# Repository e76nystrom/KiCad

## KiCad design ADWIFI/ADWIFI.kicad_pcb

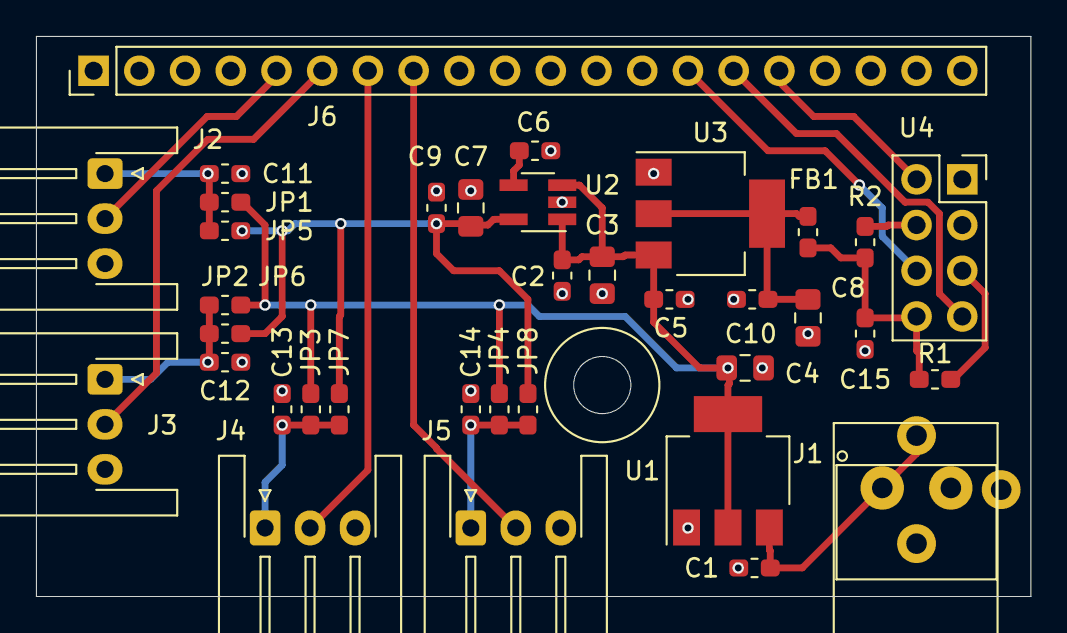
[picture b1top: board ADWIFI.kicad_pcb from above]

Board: 2 copper layers, 55.2 x 31.1 mm, 37 parts (0 on the bottom side), 20 nets.

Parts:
C1, C2, C5, C9, C10, C11, C12, C13, C14, C15: .1uf; C_0603_1608Metric_Pad1.05x0.95mm_HandSolder
C3, C4, C7, C8: 10u; C_0805_2012Metric_Pad1.15x1.40mm_HandSolder
C6: .1u; C_0603_1608Metric_Pad1.05x0.95mm_HandSolder
FB1: Ferrite_Bead; L_0603_1608Metric_Pad1.05x0.95mm_HandSolder
H1: MountingHole; MountingHole _1-8_1-4
J1: PJ-102; PJ-102-3.81mm
J2, J3, J4, J5: Conn_01x03_Female; JST_XH_S3B-XH-A-1_1x03_P2.50mm_Horizontal
J6: Conn_01x20_Male; PinHeader_1x20_P2.54mm_Vertical
JP1, JP2, JP3, JP4, JP5, JP6, JP7, JP8: Jumper_NO_Small; R_0603_1608Metric_Pad1.05x0.95mm_HandSolder
R1, R2: R; R_0603_1608Metric_Pad1.05x0.95mm_HandSolder
U1: AP1117-50; SOT-223-3_TabPin2
U2: RT9193; SOT-23-5_HandSoldering
U3: AP1117-33; SOT-223-3_TabPin2
U4: ESP8266; ESP-01

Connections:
+3V3: C7.1, C9.1, JP5.1, JP6.1, JP7.1, JP8.1, U2.5
+5V: C2.1, C3.1, C4.1, C5.1, JP1.1, JP2.1, JP3.1, JP4.1, U1.2, U2.1, U2.3, U3.3
/3.3W: C8.1, C10.1, FB1.1, U3.2
/A0: J2.2, J6.5
/A1: J3.2, J6.6
/A2: J4.2, J6.7
/A3: J5.2, J6.8
/B1-Rst: J6.14, U4.6
/B10-Tx: J6.15, U4.7
/B11-Rx: J6.16, U4.2
/BP: C6.1, U2.4
/ESP3.3: C15.1, FB1.2, R1.1, R2.1, U4.8
/VA0: C11.2, J2.1, JP1.2, JP5.2
/VA1: C12.2, J3.1, JP2.2, JP6.2
/VA2: C13.2, J4.1, JP3.2, JP7.2
/VA3: C14.2, J5.1, JP4.2, JP8.2
/Vin: C1.1, J1.1, U1.3
GND: C1.2, C2.2, C3.2, C4.2, C5.2, C6.2, C7.2, C8.2, C9.2, C10.2, C11.1, C12.1, C13.1, C14.1, C15.2, J1.2, J2.3, J3.3, J4.3, J5.3, J6.19, J6.20, U1.1, U2.2, U3.1, U4.1
unnamed: R1.2, U4.5
unnamed: R2.2, U4.4

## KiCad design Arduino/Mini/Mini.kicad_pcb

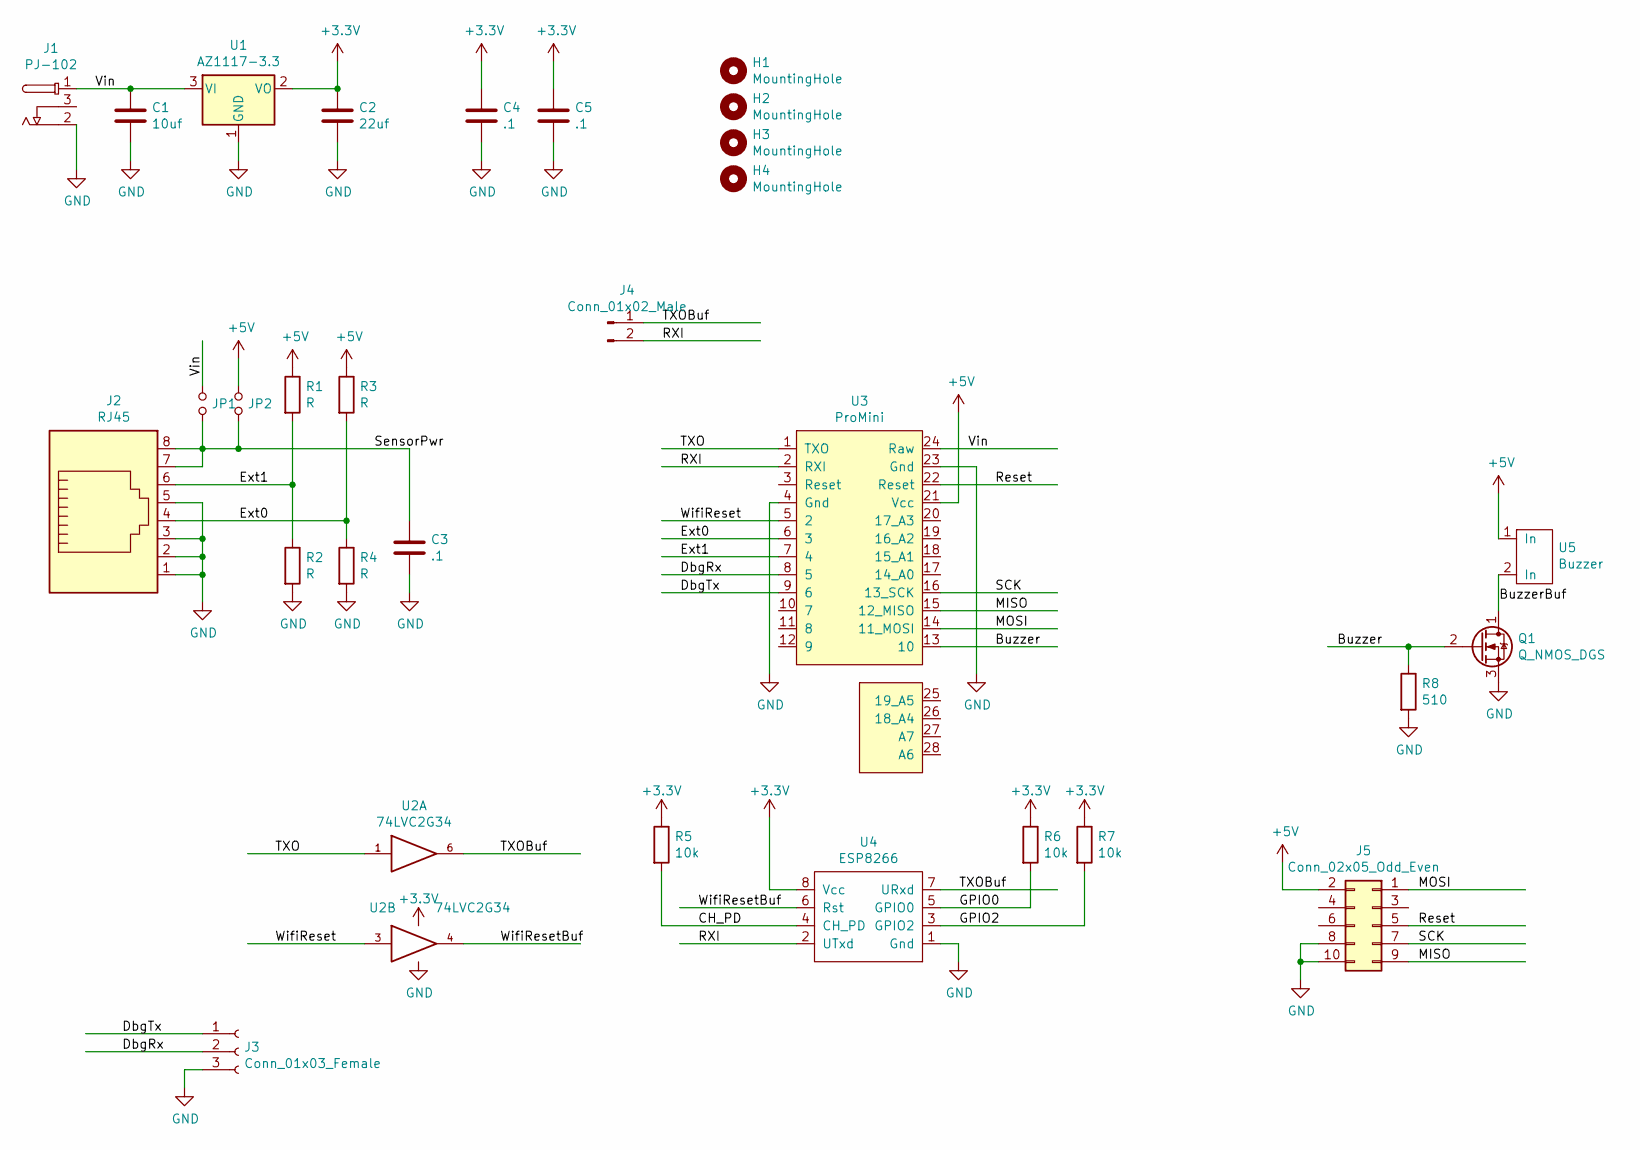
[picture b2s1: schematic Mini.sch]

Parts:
C1: 10uf; C_0805_2012Metric_Pad1.15x1.40mm_HandSolder
C2: 22uf; C_0805_2012Metric_Pad1.15x1.40mm_HandSolder
C3, C4, C5: .1; C_0805_2012Metric_Pad1.15x1.40mm_HandSolder
H1, H2, H3, H4: MountingHole; MountingHole _1-8_1-4
J1: PJ-102
J2: RJ45; RJ45_Amphenol_54602-x08_Horizontal
J3: Conn_01x03_Female; JST_EH_S3B-EH_1x03_P2.50mm_Horizontal
J4: Conn_01x02_Male; PinHeader_1x02_P2.54mm_Vertical
J5: Conn_02x05_Odd_Even; PinHeader_2x05_P2.54mm_Vertical
JP1, JP2: Jumper_NO_Small; R_0603_1608Metric_Pad1.05x0.95mm_HandSolder
Q1: Q_NMOS_DGS; SOT-23-Handsoldering
R1, R2, R3, R4: R; R_0805_2012Metric_Pad1.15x1.40mm_HandSolder
R5, R6, R7: 10k; R_0805_2012Metric_Pad1.15x1.40mm_HandSolder
R8: 510; R_0805_2012Metric_Pad1.15x1.40mm_HandSolder
U1: AZ1117-3.3; SOT-89-3_Handsoldering
U2: 74LVC2G34; SOT-23-6_Handsoldering
U3: ProMini
U4: ESP8266; ESP-01
U5: Buzzer

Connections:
+3V3: C2.1, C4.1, C5.1, R5.1, R6.1, R7.1, U1.2 (VO), U2.5 (VCC), U4.8 (Vcc)
+5V: J5.2, JP2.1, R1.1, R3.1, U3.21 (Vcc), U5.1
/Buzzer: Q1.2 (G), R8.1, U3.13 (10)
/BuzzerBuf: Q1.1 (D), U5.2
/CH_PD: R5.2, U4.4 (CH_PD)
/DbgRx: J3.2, U3.8 (5)
/DbgTx: J3.1, U3.9 (6)
/Ext0: J2.4, R3.2, R4.1, U3.6 (3)
/Ext1: J2.6, R1.2, R2.1, U3.7 (4)
/GPIO0: R6.2, U4.5 (GPIO0)
/GPIO2: R7.2, U4.3 (GPIO2)
/MISO: J5.9, U3.15 (12_MISO)
/MOSI: J5.1, U3.14 (11_MOSI)
/RXI: J4.2, U3.2 (RXI), U4.2 (UTxd)
/Reset: J5.5, U3.22 (Reset)
/SCK: J5.7, U3.16 (13_SCK)
/SensorPwr: C3.1, J2.7, J2.8, JP1.2, JP2.2
/TXO: U2.1, U3.1 (TXO)
/TXOBuf: J4.1, U2.6, U4.7 (URxd)
/Vin: C1.1, J1.1, JP1.1, U1.3 (VI), U3.24 (Raw)
/WifiReset: U2.3, U3.5 (2)
/WifiResetBuf: U2.4, U4.6 (Rst)
GND: C1.2, C2.2, C3.2, C4.2, C5.2, J1.2, J2.1, J2.2, J2.3, J2.5, J3.3, J5.8, J5.10, Q1.3 (S), R2.2, R4.2, R8.2, U1.1 (GND), U2.2 (GND), U3.4 (Gnd), U3.23 (Gnd), U4.1 (Gnd)

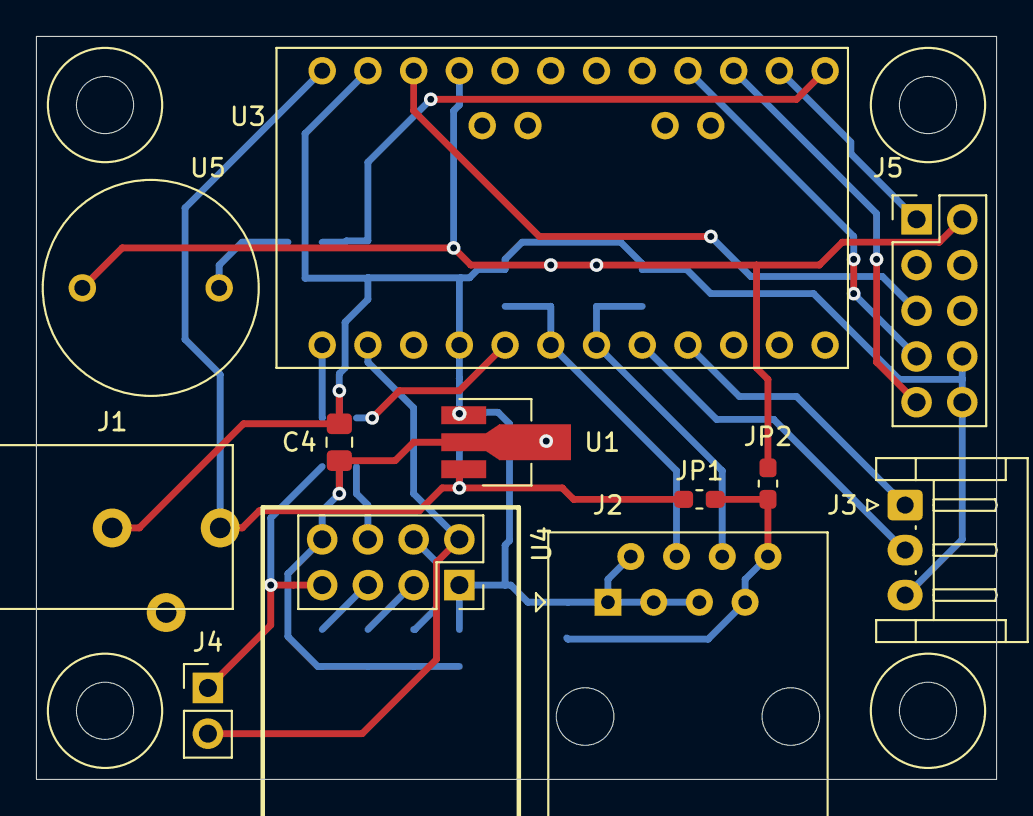
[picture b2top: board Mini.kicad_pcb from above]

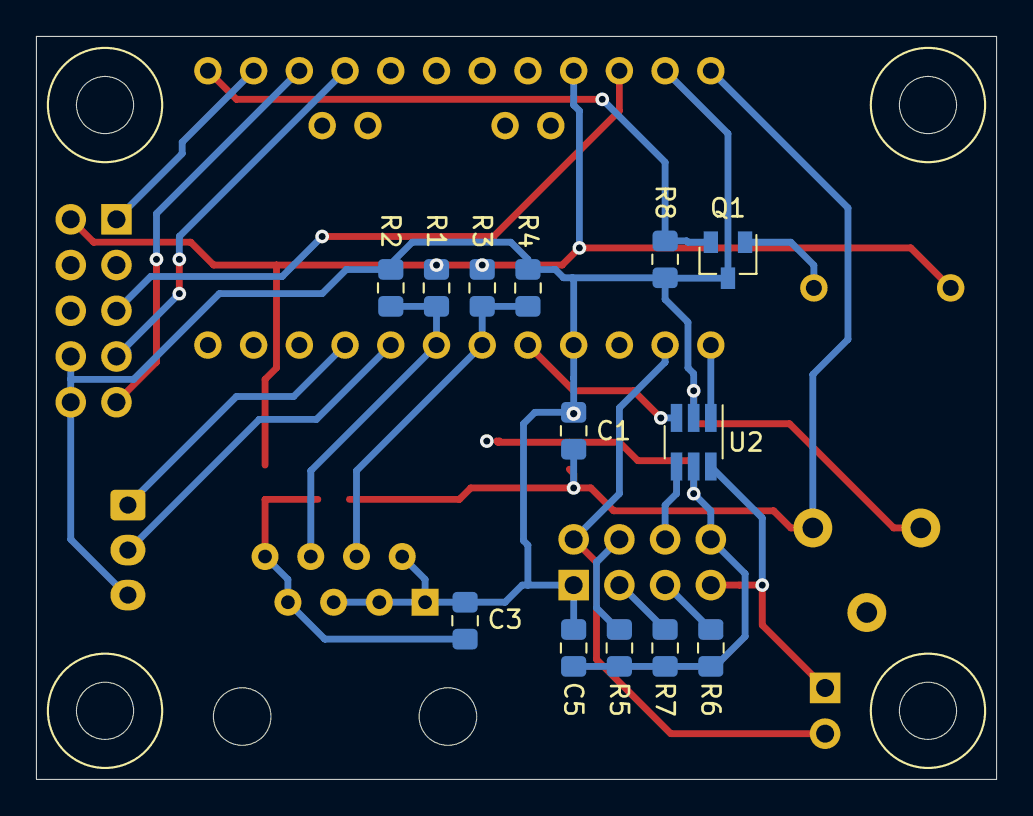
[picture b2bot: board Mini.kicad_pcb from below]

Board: 2 copper layers, 53.3 x 41.3 mm, 29 parts (13 on the bottom side), 23 nets.

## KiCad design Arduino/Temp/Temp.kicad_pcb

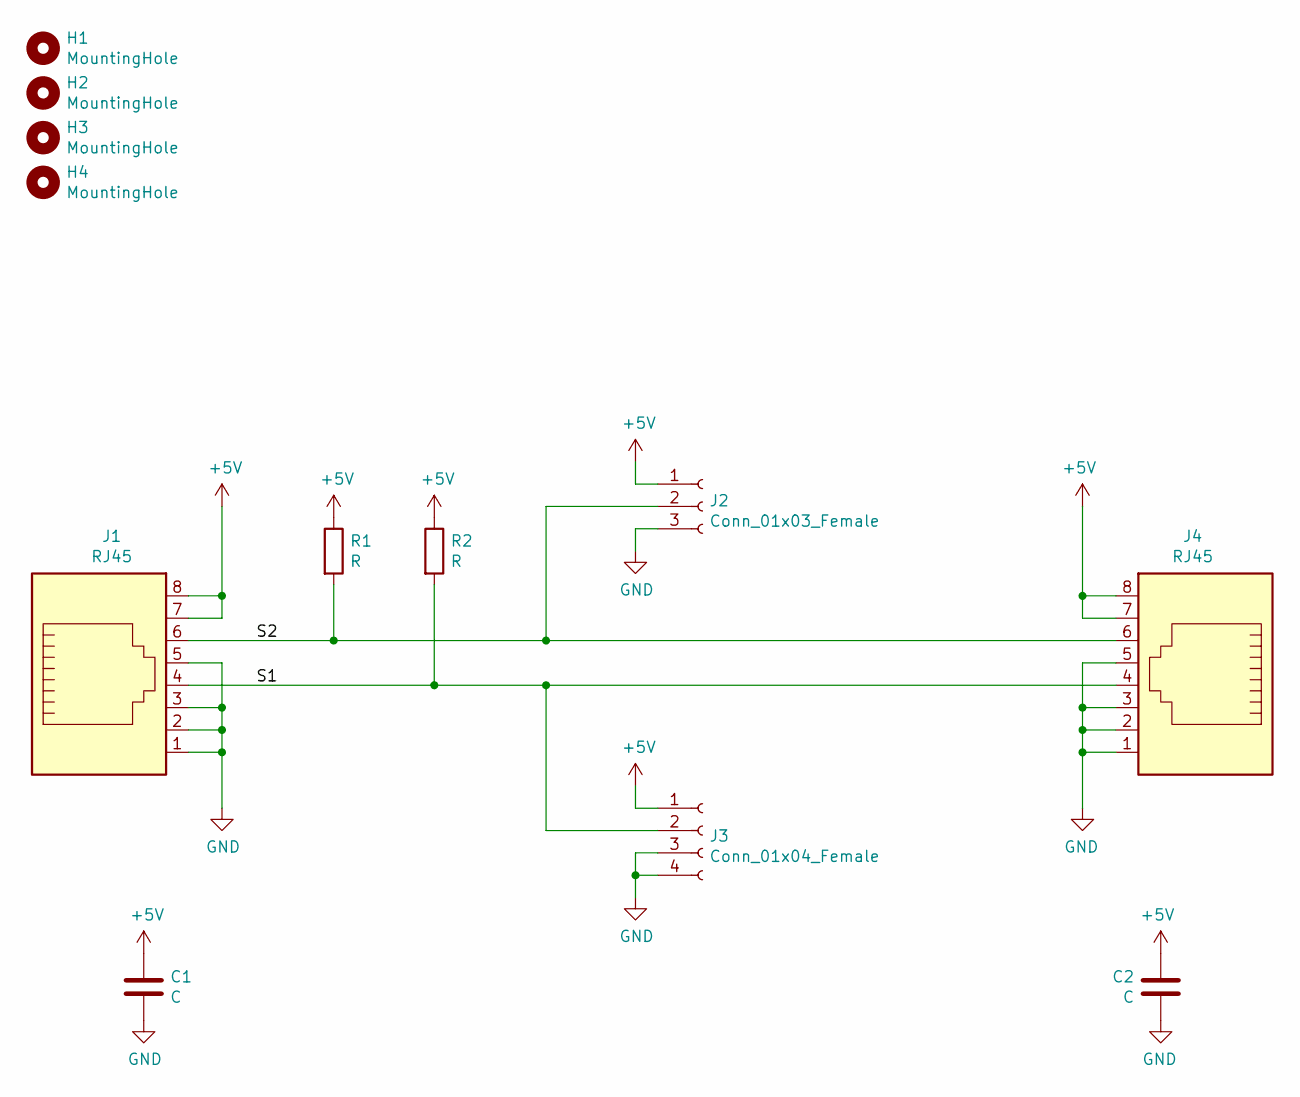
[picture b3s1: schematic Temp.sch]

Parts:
C1, C2: C; C_0805_2012Metric_Pad1.15x1.40mm_HandSolder
H1, H2, H3, H4: MountingHole; MountingHole_1-8_1-8
J1, J4: RJ45; RJ45_Amphenol_54602-x08_Horizontal
J2: Conn_01x03_Female; PinSocket_1x03_P2.54mm_Vertical
J3: Conn_01x04_Female; DHT22
R1, R2: R; R_0805_2012Metric_Pad1.15x1.40mm_HandSolder

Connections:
+5V: C1.1, C2.1, J1.7, J1.8, J2.1, J3.1, J4.7, J4.8, R1.1, R2.1
/S1: J1.4, J3.2, J4.4, R2.2
/S2: J1.6, J2.2, J4.6, R1.2
GND: C1.2, C2.2, J1.1, J1.2, J1.3, J1.5, J2.3, J3.3, J3.4, J4.1, J4.2, J4.3, J4.5

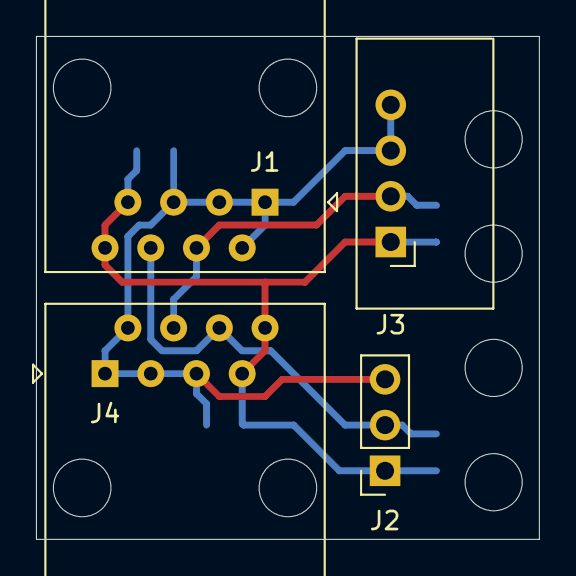
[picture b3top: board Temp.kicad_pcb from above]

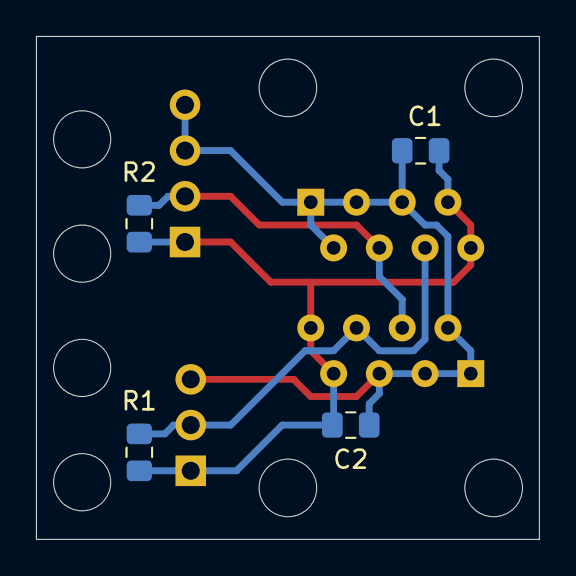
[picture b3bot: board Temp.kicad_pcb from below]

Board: 2 copper layers, 27.9 x 27.9 mm, 12 parts (4 on the bottom side), 4 nets.

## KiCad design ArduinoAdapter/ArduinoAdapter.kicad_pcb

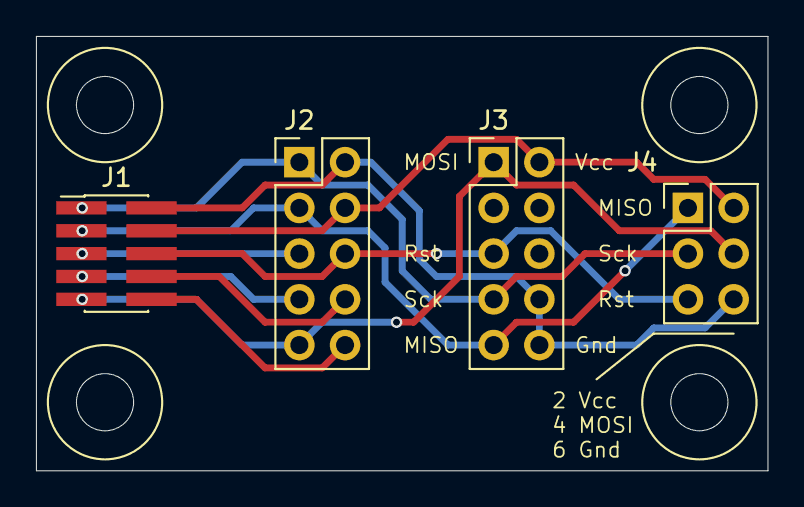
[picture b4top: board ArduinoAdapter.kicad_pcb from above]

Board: 2 copper layers, 40.6 x 24.1 mm, 8 parts (0 on the bottom side), 10 nets.

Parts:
H1, H2, H3, H4: MountingHole; MountingHole _1-8_1-4
J1: Conn_02x05_Odd_Even; PinHeader_2x05_P1.27mm_Vertical_SMD_Samtec
J2, J3: Conn_02x05_Odd_Even; PinHeader_2x05_P2.54mm_Vertical
J4: Conn_02x03_Odd_Even; PinHeader_2x03_P2.54mm_Vertical

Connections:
/Gnd: J1.2, J2.2, J3.8, J3.10, J4.6
/MISO: J1.3, J2.3, J3.9, J4.1
/MOSI: J1.9, J2.9, J3.1, J4.4
/P5: J1.5, J2.5
/P7: J1.7, J2.7
/P8: J1.8, J2.8
/P10: J1.10, J2.10
/Reset: J1.6, J2.6, J3.5, J4.5
/SCK: J1.1, J2.1, J3.7, J4.3
/Vcc: J1.4, J2.4, J3.2, J4.2

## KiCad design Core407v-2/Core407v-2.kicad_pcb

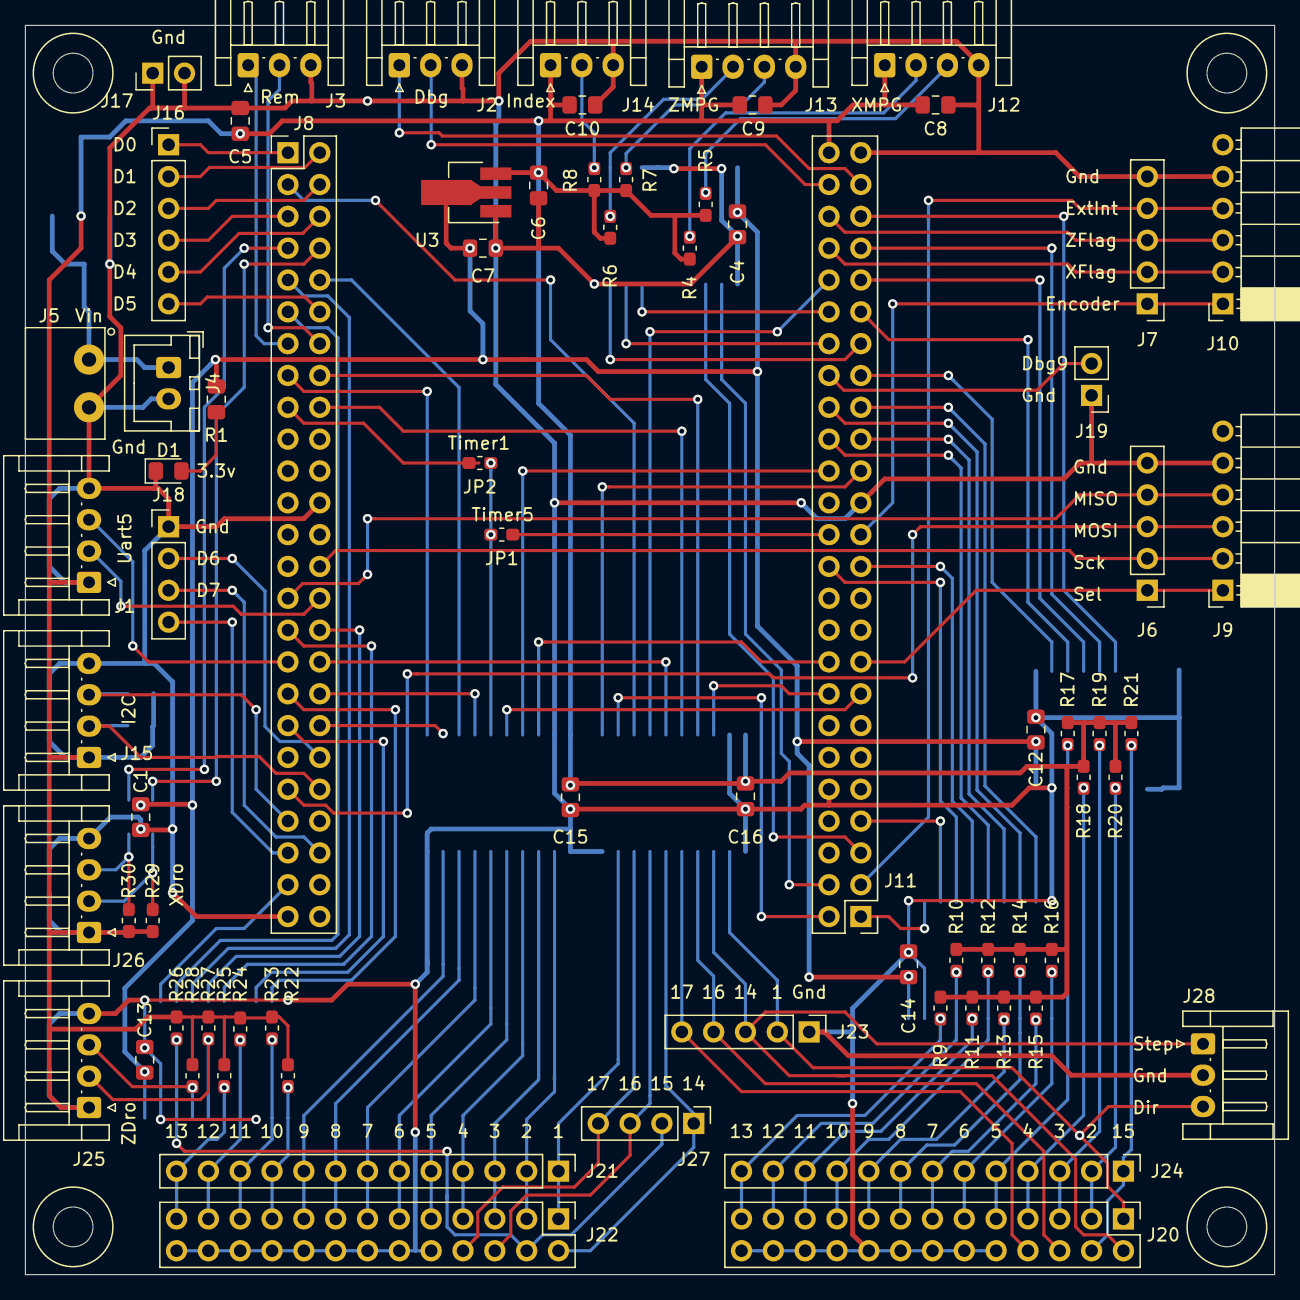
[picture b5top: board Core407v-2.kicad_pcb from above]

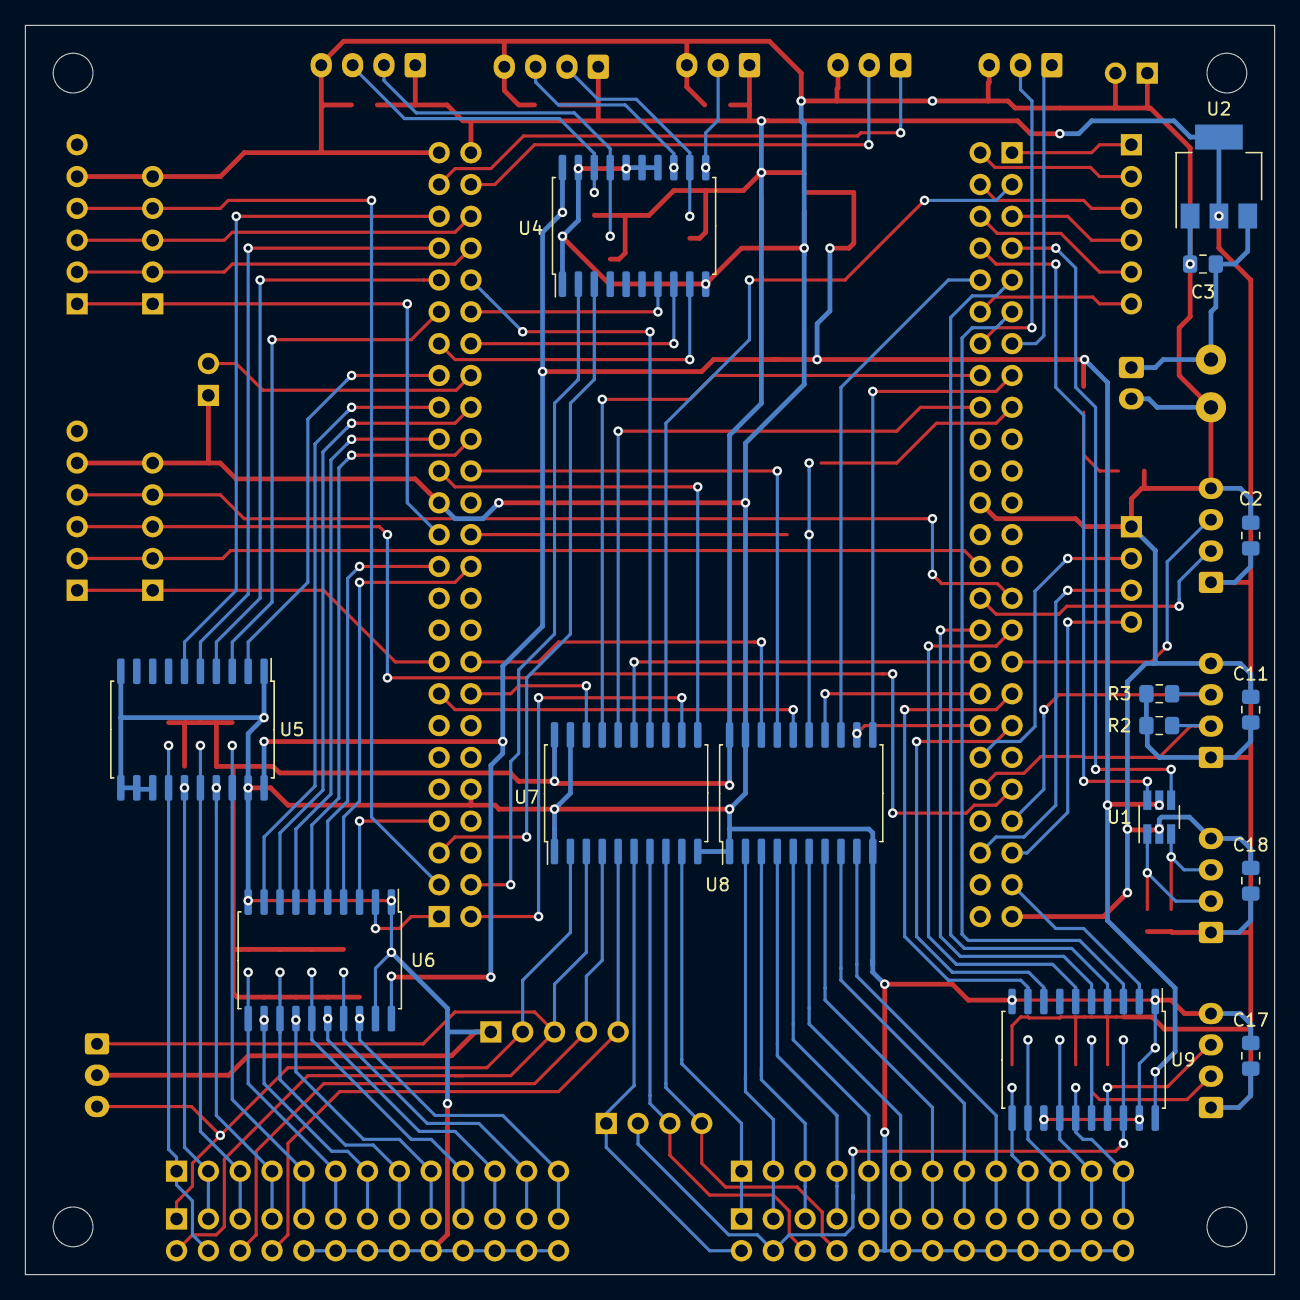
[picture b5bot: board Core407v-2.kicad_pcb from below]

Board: 2 copper layers, 99.7 x 99.7 mm, 92 parts (15 on the bottom side), 119 nets.

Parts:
C1, C2, C3, C4, C6, C8, C9, C10, C11, C12, C13, C14, C15, C16, C17, C18: .1uf; C_0805_2012Metric_Pad1.15x1.40mm_HandSolder
C5, C7: 10uf; C_0805_2012Metric_Pad1.15x1.40mm_HandSolder
D1: LED; D_0805_2012Metric_Pad1.15x1.40mm_HandSolder
H1, H2, H3, H4: MountingHole; MountingHole _1-8_1-4
J1, J12, J13, J15, J25, J26: Conn_01x04; JST_EH_S4B-EH_1x04_P2.50mm_Horizontal
J2, J3, J14, J28: Conn_01x03; JST_EH_S3B-EH_1x03_P2.50mm_Horizontal
J4: Conn_01x02; JST_XH_B2B-XH-A_1x02_P2.50mm_Vertical
J5: Conn_01x02; 2 Pin 3.81mm
J6, J7, J23: Conn_01x05_Male; PinHeader_1x05_P2.54mm_Vertical
J8: Conn_02x25_Odd_Even_Core_Left; Core407v-Left
J9, J10: Conn_01x06; PinSocket_1x06_P2.54mm_Horizontal
J11: Conn_02x25_Odd_Even_Core_Right; PinHeader_2x25_P2.54mm_Vertical
J16: Conn_01x06_Male; PinHeader_1x06_P2.54mm_Vertical
J17, J19: Conn_01x02_Male; PinHeader_1x02_P2.54mm_Vertical
J18, J27: Conn_01x04_Male; PinHeader_1x04_P2.54mm_Vertical
J20, J22: Conn_02x13_Top_Bottom; PinHeader_2x13_P2.54mm_Vertical
J21, J24: Conn_01x13_Male; PinHeader_1x13_P2.54mm_Vertical
JP1: S2_T5; R_0603_1608Metric_Pad1.05x0.95mm_HandSolder
JP2: S2_T1; R_0603_1608Metric_Pad1.05x0.95mm_HandSolder
R1: R; R_0805_2012Metric_Pad1.15x1.40mm_HandSolder
R2, R3: 4.7k; R_0805_2012Metric_Pad1.15x1.40mm_HandSolder
R4, R5, R6, R7, R8, R9, R10, R11, R12, R13, R14, R15, R16, R17, R18, R19, R20, R21, R22, R23, R24, R25, R26, R27, R28, R29, R30: 10k; R_0603_1608Metric_Pad1.05x0.95mm_HandSolder
U1: 74LVC2G34; SOT-23-6_Handsoldering
U2: AMS1117-5.0; SOT-223-3_TabPin2
U3: AMS1117-3.3; SOT-89-3_Handsoldering
U4, U5, U6, U7, U8, U9: 74HC245; SOIC-20W_7.5x12.8mm_P1.27mm

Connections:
+3V3: C1.1, C4.1, C7.1, C12.1, C13.1, C14.1, R1.1, U1.5, U3.2, U4.20, U5.20, U6.20, U9.20
+5V: C2.1, C5.1, C6.1, C8.1, C9.1, C10.1, C11.1, C15.1, C16.1, C17.1, C18.1, J1.1, J11.50, J12.1, J13.1, J14.1, J15.1, J25.1, J26.1, R2.1, R3.1, R4.1, R5.1, R6.1, R7.1, R8.1, R9.1, R10.1, R11.1, R12.1, R13.1, R14.1, R15.1, R16.1, R17.1, R18.1, R19.1, R20.1, R21.1, R22.1, R23.1, R24.1, R25.1, R26.1, R27.1, R28.1, R29.1, R30.1, U2.2, U3.3, U7.20, U8.20
/Dbg0: J8.1, J16.1
/Dbg1: J8.2, J16.2
/Dbg2: J8.4, J16.3
/Dbg3: J8.5, J16.4
/Dbg4: J8.6, J16.5
/Dbg5: J8.12, J16.6
/Dbg6: J8.40, J18.2
/Dbg7: J8.46, J18.3
/Dbg8: J8.45, J18.4
/Dbg9: J11.36, J19.2
/Dir1: J11.18, U8.18
/Dir1Buf: J21.2, J22.2, U8.2
/Dir2: J11.15, U8.16
/Dir2Buf: J21.4, J22.4, U8.4
/Dir3: J8.36, U8.14
/Dir3Buf: J21.6, J22.6, U8.6
/Dir4: J8.38, U8.12
/Dir4Buf: J21.8, J22.8, U8.8
/Dir5: J11.16, U7.18
/Encoder: J7.1, J10.1, J11.25
/ExtInt: J7.4, J10.4, J11.3
/I2C_SCL: J8.42, J15.2, R2.2
/I2C_SDA: J8.43, J15.3, R3.2
/Index2: J14.2, R8.2, U4.11
/Index2Buf: J11.37, U4.9
/JogA1: J12.2, R4.2, U4.17
/JogA1Buf: J11.5, U4.3
/JogA2: J13.2, R6.2, U4.12
/JogA2Buf: J11.38, U4.8
/JogB1: J12.3, R5.2, U4.18
/JogB1Buf: J11.4, U4.2
/JogB2: J13.3, R7.2, U4.13
/JogB2Buf: J11.40, U4.7
/LedR: D1.2, R1.2
/Pin1: J11.29, U7.11
/Pin1Buf: J21.1, J22.1, U7.9
/Pin10: J21.10, J22.10, R22.2, U9.11
/Pin10Buf: J8.35, U9.9
/Pin11: J21.11, J22.11, R23.2, U9.12
/Pin11Buf: J8.37, U9.8
/Pin12: J21.12, J22.12, R24.2, U9.14
/Pin12Buf: J8.31, U9.6
/Pin13: J21.13, J22.13, R25.2, U9.15
/Pin13Buf: J8.32, U9.5
/Pin14: J11.42, U7.14
/Pin14Buf: J22.14, J27.1, U7.6
/Pin15: J22.15, J27.2, R26.2, U9.18
/Pin15Buf: J8.47, U9.2
/Pin16Buf: J22.16, J27.3, U7.7
/Pin16_T12_Ch1: J8.3, U7.13
/Pin17: J11.2, U7.12
/Pin17Buf: J22.17, J27.4, U7.8
/PinA1Buf: J20.1, J23.2, J28.3, U7.2
/PinA2: J20.2, J24.2, R20.2, U5.15
/PinA2Buf: J11.43, U5.5
/PinA3: J20.3, J24.3, R19.2, U5.16
/PinA3Buf: J11.41, U5.4
/PinA4: J20.4, J24.4, R18.2, U5.17
/PinA4Buf: J11.39, U5.3
/PinA5: J20.5, J24.5, R17.2, U5.18
/PinA5Buf: J11.35, U5.2
/PinA6: J20.6, J24.6, R16.2, U6.11
/PinA6Buf: J11.33, U6.9
/PinA7: J20.7, J24.7, R15.2, U6.12
/PinA7Buf: J11.34, U6.8
/PinA8: J20.8, J24.8, R14.2, U6.13
/PinA8Buf: J11.31, U6.7
/PinA9: J20.9, J24.9, R13.2, U6.14
/PinA9Buf: J11.32, U6.6
/PinA10: J20.10, J24.10, R12.2, U6.15
/PinA10Buf: J11.23, U6.5
/PinA11: J20.11, J24.11, R11.2, U6.16
/PinA11Buf: J11.24, U6.4
/PinA12: J20.12, J24.12, R10.2, U6.17
/PinA12Buf: J11.7, U6.3
/PinA13: J20.13, J24.13, R9.2, U6.18
/PinA13Buf: J11.1, U6.2
/PinA14Buf: J20.14, J23.3, J28.1, U7.3
/PinA15: J20.15, J24.1, R21.2, U5.14
/PinA15Buf: J11.45, U5.6
/PinA16: J8.18, U7.16
/PinA16Buf: J20.16, J23.4, U7.4
/PinA17: J8.34, U7.15
/PinA17Buf: J20.17, J23.5, U7.5
/S1_T2_Ch1: J11.30, U8.17
/S2_T5-1: JP1.2, JP2.1, U8.15
/S2a_T5_Ch4: J11.26, JP1.1
/S2b_T1_Ch1: J8.17, JP2.2
/S3_T4_Ch2: J8.10, U8.13
/S4_T3_Ch3: J8.15, U8.11
/S5_T8_Ch4: J8.16, U7.17
/SPI_MISO: J6.4, J8.29, J9.4
/SPI_MOSI: J6.3, J8.41, J9.3
/SPI_SCK: J6.2, J8.28, J9.2
/Sel: J6.1, J9.1, J11.17
/Step1Buf: J21.3, J22.3, U8.3
/Step2Buf: J21.5, J22.5, U8.5
/Step3Buf: J21.7, J22.7, U8.7
/Step4Buf: J21.9, J22.9, U8.9
/Uart3Rx: J2.2, J11.48
/Uart3Tx: J2.1, J11.47
/Uart5Rx: J1.3, J8.33
/Uart5Tx: J1.2, J8.30
/Uart6Rx: J3.2, J8.14
/Uart6Tx: J3.1, J8.13
/Vin: C3.1, J4.1, J5.1, U2.3
/XA: J26.2, R29.2, U1.1
/XABuf: J8.8, U1.6
/XB: J26.3, R30.2, U1.3
/XBBuf: J8.7, U1.4
/XFlag: J7.2, J10.2, J11.44
/ZA: J25.2, R27.2, U9.16
/ZABuf: J8.11, U9.3
/ZB: J25.3, R28.2, U9.17
/ZBBuf: J8.9, U9.4
/ZFlag: J7.3, J10.3, J11.46
GND: C1.2, C2.2, C3.2, C4.2, C5.2, C6.2, C7.2, C8.2, C9.2, C10.2, C11.2, C12.2, C13.2, C14.2, C15.2, C16.2, C17.2, C18.2, D1.1, J1.4, J2.3, J3.3, J4.2, J5.2, J6.5, J7.5, J8.24, J8.49, J9.5, J10.5, J11.10, J11.27, J11.49, J12.4, J13.4, J14.3, J15.4, J17.1, J17.2, J18.1, J19.1, J20.18, J20.19, J20.20, J20.21, J20.22, J20.23, J20.24, J20.25, J20.26, J22.18, J22.19, J22.20, J22.21, J22.22, J22.23, J22.24, J22.25, J22.26, J23.1, J25.4, J26.4, J28.2, U1.2, U2.1, U3.1, U4.1, U4.10, U4.14, U4.15, U4.16, U4.19, U5.1, U5.10, U5.11, U5.12, U5.13, U5.19, U6.1, U6.10, U6.19, U7.1, U7.10, U7.19, U8.1, U8.10, U8.19, U9.1, U9.10, U9.13, U9.19

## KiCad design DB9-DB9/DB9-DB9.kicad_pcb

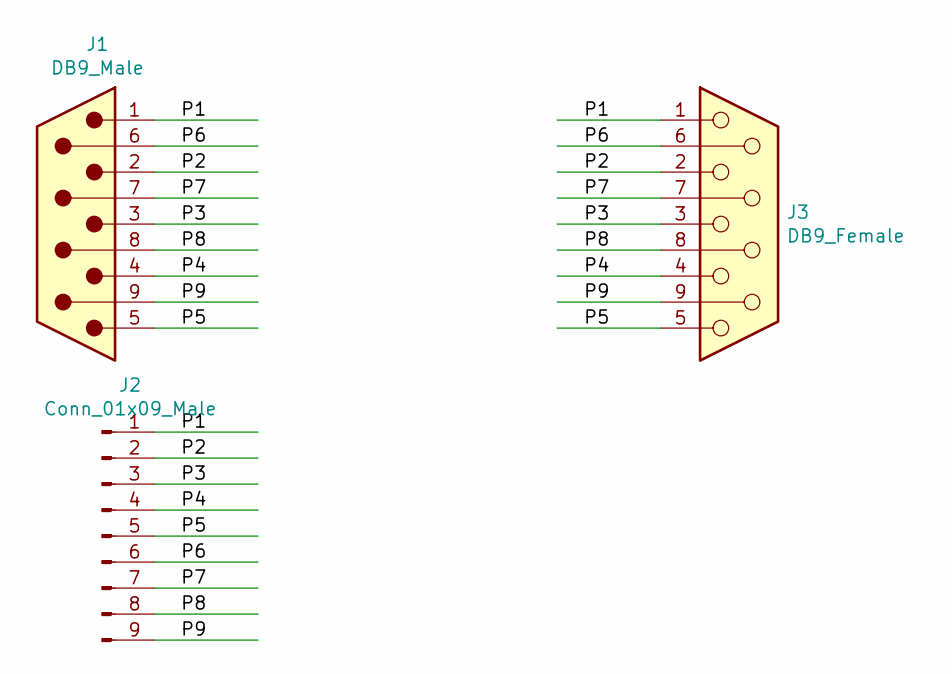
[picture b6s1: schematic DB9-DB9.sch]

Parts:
J1: DB9_Male; DSUB-9_Male_Horizontal_P2.77x2.84mm_EdgePinOffset4.94mm_Hou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
J2: Conn_01x09_Male; PinHeader_1x09_P2.54mm_Vertical
J3: DB9_Female; DSUB-9_Female_Horizontal_P2.77x2.84mm_EdgePinOffset4.94mm_H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

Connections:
/P1: J1.1, J2.1, J3.1
/P2: J1.2, J2.2, J3.2
/P3: J1.3, J2.3, J3.3
/P4: J1.4, J2.4, J3.4
/P5: J1.5, J2.5, J3.5
/P6: J1.6, J2.6, J3.6
/P7: J1.7, J2.7, J3.7
/P8: J1.8, J2.8, J3.8
/P9: J1.9, J2.9, J3.9

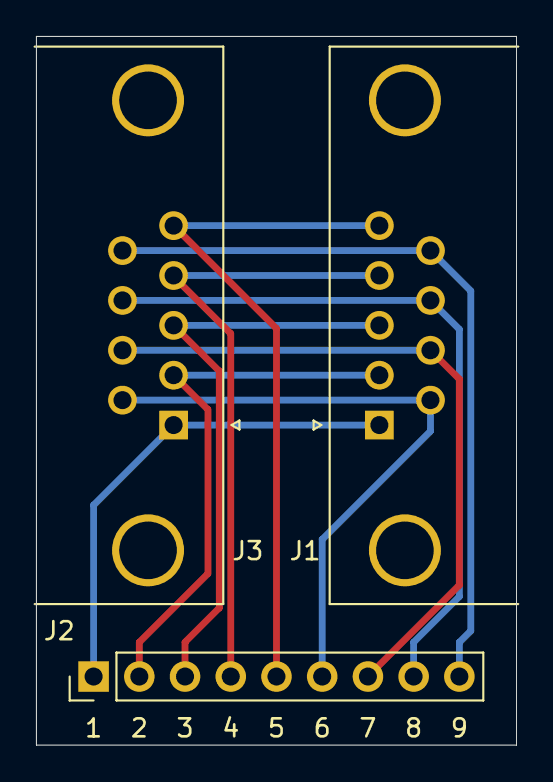
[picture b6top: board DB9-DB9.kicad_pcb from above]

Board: 2 copper layers, 26.7 x 39.4 mm, 3 parts (0 on the bottom side), 9 nets.
